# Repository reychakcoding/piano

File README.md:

Hi guys! This is my MIDI Piano for Week 3 of Half Life by Hack Club. 
This was definitely harder than the first PCB but it was still fun in a way! 
I learned some things about routing ratnests, designing custom footprints, and different types of neopixels.
Here are some images of my project!

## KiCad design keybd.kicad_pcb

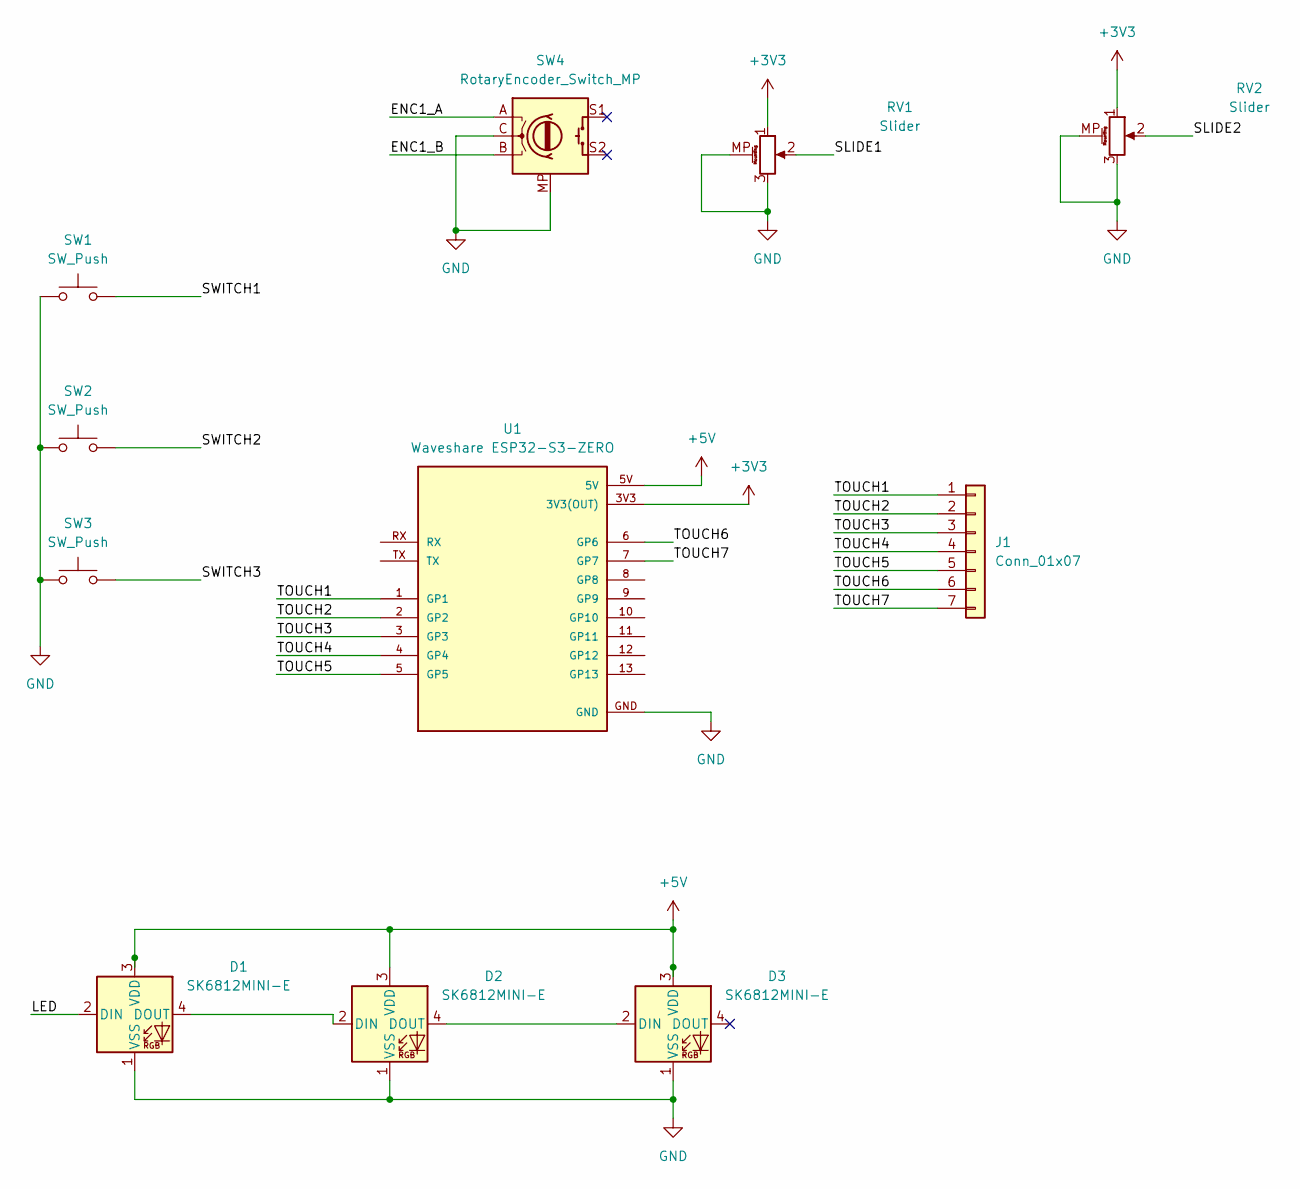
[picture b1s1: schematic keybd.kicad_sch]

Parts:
D1, D2, D3: SK6812MINI-E; LED_SK6812MINI-E_3.2x2.8mm_P1.5mm_ReverseMount
J1: Conn_01x07; Untitled
RV1, RV2: Slider; Potentiometer_Bourns_PTA1543_Single_Slide
SW1, SW2, SW3: SW_Push; Kailh Choc Low-Profile Switches
SW4: RotaryEncoder_Switch_MP; RotaryEncoder_Alps_EC11E-Switch_Vertical_H20mm
U1: Waveshare ESP32-S3-ZERO; Waveshare ESP32-S3-Zero; PARTREV NA

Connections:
+3V3: RV1.1, RV2.1, U1.3V3 (3V3(OUT))
+5V: D1.3 (VDD), D2.3 (VDD), D3.3 (VDD), U1.5V
/ENC1_A: SW4.A
/ENC1_B: SW4.B
/LED: D1.2 (DIN)
/SLIDE1: RV1.2
/SLIDE2: RV2.2
/SWITCH1: SW1.2
/SWITCH2: SW2.2
/SWITCH3: SW3.2
/TOUCH1: J1.1, U1.1 (GP1)
/TOUCH2: J1.2, U1.2 (GP2)
/TOUCH3: J1.3, U1.3 (GP3)
/TOUCH4: J1.4, U1.4 (GP4)
/TOUCH5: J1.5, U1.5 (GP5)
/TOUCH6: J1.6, U1.6 (GP6)
/TOUCH7: J1.7, U1.7 (GP7)
GND: D1.1 (VSS), D2.1 (VSS), D3.1 (VSS), RV1.3, RV1.MP (MountPin), RV2.3, RV2.MP (MountPin), SW1.1, SW2.1, SW3.1, SW4.C, SW4.MP, U1.GND
unnamed: D1.4 (DOUT), D2.2 (DIN)
unnamed: D2.4 (DOUT), D3.2 (DIN)

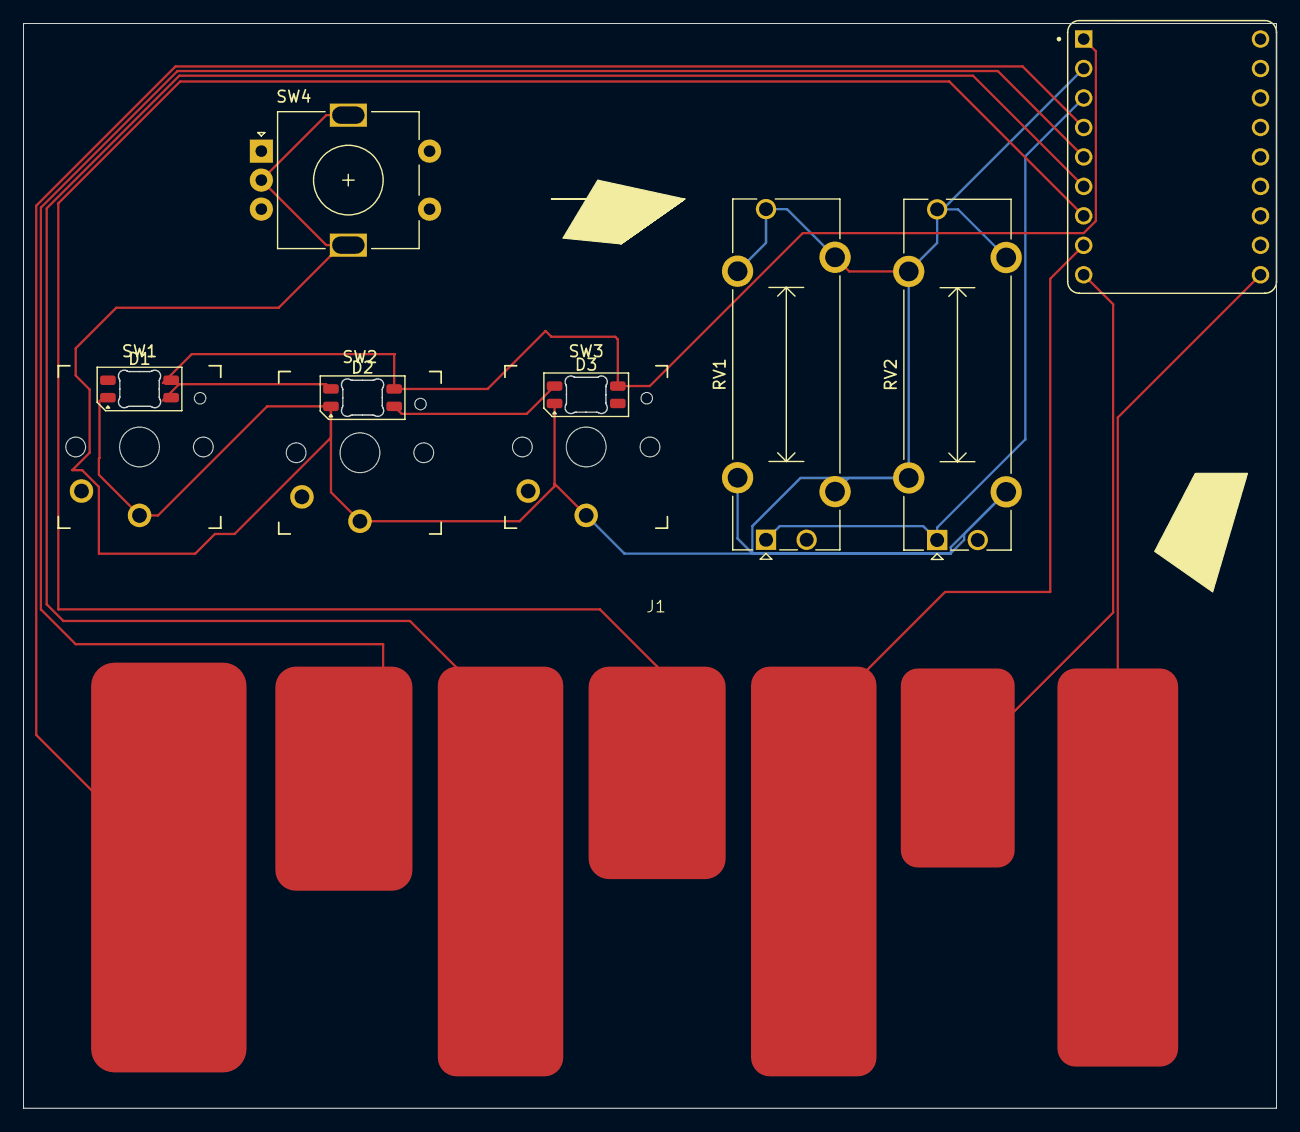
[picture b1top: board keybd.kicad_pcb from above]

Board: 2 copper layers, 108.0 x 93.5 mm, 11 parts (0 on the bottom side), 12 nets.
